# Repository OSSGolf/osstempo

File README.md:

# Tempo Trainer

A TempoStik-style tempo trainer: a WS2812B LED strip animates a swing so the
user follows a moving dot to groove their tempo. Two modes — **putting** (2:1)
and **full swing** — selectable over BLE. No audio.

## Goal

A white LED "comet" sweeps along the strip following a pendulum/arc model so the
motion feels like a real stroke. The user matches their club/putter head to the
dot to train tempo and stroke length. Reference dots (green = ball/impact,
amber = top of backswing, red = full extent, optional purple = full-swing
weight-shift aim) orient the golfer before each rep.

- **Putt mode:** comet sweeps center → amber (backswing), eases to a stop, then
  accelerates back through center (impact) and out the far side (follow-through).
- **Full mode:** models a full swing's *arc projected onto the 1D strip* (see
  [Animation models](#animation-models)). Lets a 1 m strip represent a swing that
  goes back and up behind the golfer.

## Build guides

Two ways to build it, same firmware and app. See [`docs/`](docs/):

- [**docs/full-diy/**](docs/full-diy/) - bare ESP32 dev board, strip, one resistor
  and one cap on a breadboard. Lowest cost.
- [**docs/dig2go/**](docs/dig2go/) - pre-assembled [QuinLED-Dig2go]. Screw in three
  wires, flash, done.
- [**pcb/**](pcb/README.md) - the ESP32 carrier PCB (v1.2): the dev board drops into two
  sockets, JLCPCB places the passives, you hand-solder eleven marked pins. Renders, build
  pipeline and the JLCPCB order files live there; [`pcb_build_spec.md`](pcb_build_spec.md)
  is the board spec.

Each folder has a bill of materials, a wiring and flashing guide, and a pinned,
ready-to-flash sketch. The sections below are the full hardware and firmware spec
that both builds share.

[QuinLED-Dig2go]: https://quinled.info/quinled-dig2go/

## Hardware

- **MCU:** ESP32 classic (ESP-WROOM-32, 30-pin dev board, micro-USB). BLE used, not WiFi.
  USB-UART chip is a **CP2102** (Silicon Labs).
- **LED strip:** WS2812B, **144 LEDs on a ~1 m strip (144 LEDs/m)**, bare PCB
  12 mm wide x 2.2 mm tall, 5 V. (~0.69 cm per LED; half-strip ≈ 50 cm each side.)
- **Mounting:** 12 mm aluminum LED channel with frosted diffuser (self-sourced).
  2020 extrusion was rejected as the light channel (T-slot opening ~6 mm is too
  narrow for the 12 mm strip, and bare aluminum gives no diffusion).
- **Power:** micro-USB from a power bank or 5 V wall adapter. **A 2 A supply is
  recommended.** The strip is powered through the board's 5 V passthrough pin.
  The comet animation is low-draw (~100-300 mA), so the full-strip ~8 A worst
  case does not apply — but do **not** run an all-LEDs-on white pattern on 2 A.
- **Protoboard:** the 30-pin ESP32 is too wide for one standard breadboard — it
  straddles **two breadboards** (one row of pins on each) so the outer holes stay
  free.

## Wiring

| From | To |
|---|---|
| `GPIO5` (labeled `D5`) | 470 ohm resistor -> strip DIN |
| `VIN` pin (the 5 V passthrough; *not* `3V3`) | strip 5V (+ breadboard red rail) |
| `GND` | strip GND (common ground, blue rail) |
| 1000 uF cap | across 5V/GND at strip input (stripe / short leg to GND) |

- **`VIN` is the 5 V passthrough.** On the 30-pin board the silkscreen labels it
  `VIN` (not `5V`); it carries USB 5 V out to the strip. Do not use `3V3`.
- **Level shifter (SN74HCT245) is on hand but NOT needed** — the bare 3.3 V data
  line drives the strip cleanly (no first-pixel flicker observed). Add it on the
  `GPIO5 -> DIN` line only if flicker/wrong colors appear later.
- `GPIO5` was chosen as an exposed pin on the 30-pin board. Feed the strip at the
  DIN end (follow the data-direction arrow).

### macOS USB note

The board appears as a serial port (`/dev/cu.usbserial-*` or
`/dev/cu.SLAB_USBtoUART`) only when:

1. The **CP210x VCP driver** is installed **and approved** in
   *System Settings -> Login Items & Extensions -> Driver Extensions* (macOS
   Sequoia moved the approval there; a reboot alone does not approve it).
2. A **data-capable USB cable** is used. A charge-only micro-USB cable lights the
   board's red power LED but never enumerates on USB — the single most common
   "board not detected" cause. Verify with `ls /dev/cu.*` after plugging in.

## Firmware

- **Language / libs:** Arduino C++ (`.ino`), [FastLED], ESP32 core BLE
  (`BLEDevice` / `BLEServer`) and `Preferences` (NVS). FastLED is the only
  Library Manager install; BLE + Preferences ship with the ESP32 core.
- **Board target:** "ESP32 Dev Module."
- **Partition scheme:** **"Huge APP (3MB No OTA/1MB SPIFFS)"** — BLE + FastLED
  exceed the default app partition.
- **Upload:** micro-USB, 115200 baud. Hold **BOOT** if upload stalls at
  `Connecting...`. The sketch boots straight into the continuous loop (no BLE
  needed to run); BLE is only for customization.
- **File:** `tempo_trainer/tempo_trainer.ino`.

## Animation models

Center LED (index ~71/72) = ball / impact. Each rep runs a get-ready **countdown**
(the green impact LED pulses smoothly N times, 1 s each, with the aim dots lit) and
then the stroke, auto-repeating after a rest gap. During the stroke the comet is
**bounded** by the impact and aim markers (the green/amber "rails", toggle `000e`):
it emerges from the ball and parks at the backswing point rather than overshooting.

### Putt mode (pendulum)

1. **Get-ready countdown:** the green ball pulses smoothly N times (1 s each,
   N = `round(get-ready ms / 1000)`), with the amber aim dot lit so you can set up.
2. **Backswing:** comet center -> amber with `sin` easing (fast leaving center,
   decelerating to a stop), **bounded to `[impact, amber]`** — it emerges from the
   ball and parks at the amber without overshooting either marker.
3. **Drop to impact:** comet amber -> center over `downswing ms` (the tempo
   number; ratio = backswing:downswing), shaped by `release`. Fastest at impact;
   flows **through** impact (no hitch) into the follow-through.
4. **Follow-through:** center -> `-reach` over `follow-thru ms`, decelerating.
5. **Hold** at the finish, then **rest**, repeat.

With `rails lit` (`000e`) on, the green impact and amber backswing dots stay lit
throughout as the bounding "walls"; off, the amber shows until reached (legacy look).

### Full mode (arc projected onto the strip)

A full swing's clubhead traces an arc. Projected onto the 1D strip its position
is **non-monotonic**: it reaches max width (**red**, at the strip end) around
waist height, then comes up/in to the top of backswing (**amber**, inboard of
red). The downswing retraces back out to red before dropping to impact.

```
 followRed              center            amber          backRed
   (red)                (green)          (amber)          (red)
   |---------------------|----------------|----------------|
   far end             impact         top of back       near end / max width

 1. Backswing:   center -> backRed -> backAmber       (out to max width, up to top)
    [top pause]
 2. Downswing:   backAmber -> backRed -> center        (back out, then to impact)
 3. Follow-thru: center -> followRed                   (to the far end; no follow amber)
 4. Hold, rest, repeat
```

Easing keeps velocity zero at the turnarounds (both red visits, the top) and
maximal at center (impact), so the projection reads like a real swing.

#### Aiming dot (purple, full swing, optional)

An optional **purple** secondary dot (`000f`-`0011`, per-mode, full only) gives a
weight-shift / hit-down reminder for irons. It defaults **off**; when enabled it
sits 2 LEDs to the **target side** of impact (toward the finish) and never overlaps
the ball, amber, or red dots. It **appears** at a configurable stroke moment (`0011`: 0 address / 1 top
of backswing (default) / 2 start of downswing / 3 impact) and **stays lit until the
next rep**, independent of the `rails lit` toggle. Position (`0010`) is any LED that
is not already a marker.

### Release (acceleration profile)

Per Grober's pendulum framework, the dominant acceleration lever is the **tempo
ratio** (backswing:downswing) — already exposed via the two times. The one
remaining physical degree of freedom is the **release / lag**: how the downswing's
speed builds between the top and impact. `release` (`000c`, per-mode) blends the
drop-to-impact from a **free pendulum** (0: smooth, velocity peaks gently at
impact, putting-like) to a **late lag release** (100: the comet hangs near the top,
then snaps through impact). It reshapes only the drop-to-impact segment and never
changes tempo (impact still lands on time). Defaults: putt 0, full 55.

## Profiles & persistence

- **Two profiles** (putt / full), each with its own `backswing ms`,
  `downswing ms`, `reach`, and `top-hold ms`. Switching mode restores that mode's
  settings.
- **Global settings** (shared): brightness, get-ready ms, finish-hold ms, rest ms.
- All settings are **persisted to flash (NVS)** and reload on boot. Writes are
  debounced (~1.5 s) so live preview-slider dragging doesn't wear the flash.
- `control` is **not** persisted — the device always boots into loop mode.

#### Reversing the stick (180 flip)

`0014` runs the stroke the other way down the strip, for a left-hander or a stick lying the
other way round. It mirrors the **finished frame** on its way out, `i -> NUM_LEDS-1-i`, at the
firmware's single output choke point (`showFrame()`), so every element flips together -- comet
head and tail, green ball, amber top-of-backswing, both red extents, the purple aim dot, the
get-ready pulse, the idle dot -- and nothing in the stroke math changes. Reflection about index
`(NUM_LEDS-1)/2` *is* reflection about `CENTER`, so the picture stays self-consistent; the green
ball sits half an LED above centre normally and half an LED below it reversed, which is the exact
mirror image rather than an off-by-one.

Flipping mid-stroke is safe and needs no special handling: the renderer holds no temporal state,
so frame N draws logical and frame N+1 draws mirrored, both at the same cycle time. The comet
lands at its mirror position with identical phase -- a reflection in space, never a jump in time.
Worst case it is visible one render tick later (<=12 ms while running, <=20 ms idle), plus the
BLE round trip; a phone write with response is typically another 60-130 ms.

Two states would otherwise give no feedback at all -- idle lights a single dim centre pixel, and
the rest gap lights nothing -- so for 1.2 s after a flip both paint the mode's static dot map
instead. The amber dot jumping to the other side of the ball is the answer to "which way does it
run now?".

**It is device-local.** Orientation describes how *that* stick is lying, so it is deliberately
not carried in the sync beacon: two sticks in a set can point opposite ways, and a leader can
never rotate a follower's strip. Consequence: a follower goes BLE-quiet while in a set, so set
orientation **before** joining. It persists in NVS, including across a follower's revert.

It is also the one characteristic the iOS app treats as **optional**, so a stick flashed before
`0014` existed still connects and works -- only the reverse toggle is disabled.

## BLE GATT

- **Service:** `6e400001-b5a3-f393-e0a9-e50e24dcca9e`
- **Device name:** `PuttTempo`

| UUID tail | Param | Type | Range / units | Scope | Default (putt / full) |
|---|---|---|---|---|---|
| 0002 | backswing ms | uint16 LE | 100-5000 | per-mode | 700 / 900 |
| 0003 | downswing ms (top→impact) | uint16 LE | 100-5000 | per-mode | 350 / 300 |
| 0004 | reach (amber) | uint8 | 1-71 LEDs from center | per-mode | 58 / 60 |
| 0005 | brightness | uint8 | 0-255 | global | 40 |
| 0006 | control | uint8 | 0 idle / 1 loop / 2 single / 3 preview | runtime | 1 |
| 0007 | get-ready ms | uint16 LE | 0-10000 (countdown: round(ms/1000) impact pulses) | global | 1000 |
| 0008 | finish hold ms | uint16 LE | 0-10000 | global | 600 |
| 0009 | rest ms | uint16 LE | 0-20000 | global | 3000 |
| 000a | mode | uint8 | 0 putt / 1 full | persisted | 0 |
| 000b | top-hold ms | uint16 LE | 0-2000 | per-mode | 0 / 150 |
| 000c | release | uint8 | 0-100 (0 pendular .. 100 lag) | per-mode | 0 / 55 |
| 000d | follow-thru ms | uint16 LE | 0-10000 (impact→finish) | per-mode | 350 / 300 |
| 000e | rails lit | uint8 | 0/1 (keep impact+aim dots lit) | global | 1 |
| 000f | aim2 enabled | uint8 | 0/1 (purple weight-shift dot, full only) | per-mode | 0 / 0 |
| 0010 | aim2 position | uint8 | 1-142 (absolute LED index) | per-mode | 70 / 70 |
| 0011 | aim2 when | uint8 | 0 address / 1 top / 2 downswing / 3 impact | per-mode | 1 / 1 |
| 0014 | flip | uint8 | 0 normal / 1 mirrored end-for-end | global, device-local | 0 |

uint16 values are little-endian (e.g. 700 = `BC 02`). Per-mode writes apply to
whichever mode is currently selected (`000a`); switching `000a` refreshes the
per-mode characteristics so a read returns that mode's saved values.

- **`0006` (control) supports NOTIFY** — subscribe to get device-side state
  changes pushed (e.g. a single stroke auto-resetting to idle).
- **Discovery:** the device advertises the **service UUID** (filter scans on it)
  and broadcasts the name `PuttTempo` in the scan response. iOS/CoreBluetooth
  clients should scan by service UUID, not name.

### Setting the backswing point (live preview)

1. Write `000a` = mode (`00` putt / `01` full).
2. Write `0006` = `03` (preview) -> the strip shows the static dot map.
3. Write `0004` = reach in LEDs and watch the **amber dot move live**; park it
   where the backswing should stop.
4. Write `0006` = `01` (loop) -> runs strokes; the value auto-saves ~1.5 s later.

Drive it from a phone with **nRF Connect** (scan -> connect to `PuttTempo` ->
write characteristics), or a Web Bluetooth page (TODO below).

## Clients

- **Web Bluetooth page** (`web/index.html`) — single self-contained control page.
- **iOS app** (SwiftUI + CoreBluetooth) in the
  [osstempo-ios repo](https://github.com/OSSGolf/osstempo-ios) —
  native controller with numeric tuning (tap to type or hold to adjust), per-value
  strip diagrams, a follow-through link, a live reach drag, the get-ready countdown /
  rails toggle, and the on-strip stroke visualizer. Dev-only (no App Store).

## Gotchas / lessons learned

- **GATT handle budget.** ESP32 Arduino `createService(uuid)` defaults to **15 handles**
  and *silently truncates* the characteristic table after ~7 chars, and the Arduino BLE wrapper
  does not check the error. Symptom: a client discovers only the first 6-7 characteristics and
  rejects the device as incompatible -- indistinguishable from the stale-GATT-cache symptom
  below, so you pay the debugging cost twice. Count it exactly every time you add one:
  1 (service) + chars x 2 + 1 per CCCD. Today that is `1 + 19x2 + 2 = 41`, against the 48
  reserved by `createService(BLEUUID(SVC_UUID), 48)` -- room for 3 more before it must rise.
- **`FastLED.show()` must appear exactly once**, inside `showFrame()`. That is what makes the
  180 flip total: the mirror is applied to the finished buffer, so no LED element can escape it
  -- but only while every render path latches through that one function. `FastLED.clear(true)`
  is banned for the same reason (it calls `showColor()`, a second output path that bypasses the
  frame buffer entirely), as is `FastLED.clear()` (it clears the array bound to the controller,
  which is the *physical* buffer, not the logical frame -- use `clearLeds()`).
  `firmware_tests/check_show_chokepoint.sh` enforces all of this; a compile cannot.
- **`FastLED.show()` returns before the strip is latched.** It is asynchronous, and its internal
  yield can deschedule the calling task for milliseconds. The renderer composes into `leds[]` and
  `showFrame()` copies that into a separate `physLeds[]` for FastLED, so the shared frame is never
  transiently inconsistent -- which is why the flip does not mirror `leds[]` in place.
- **iOS caches the GATT table.** After adding/removing a characteristic and re-flashing,
  iOS serves the *stale* cached service list — toggle the iPhone's Bluetooth off/on (or forget
  the device) to force fresh discovery, or you'll see the old characteristic set.
- **Brightness 0 bricks the strip across reboots.** `brightness` is persisted and was not
  floored on load, so a persisted 0 made the strip invisibly dark on every boot. `loadParams()`
  now floors it (`constrain(brightness, 8, 255)`); runtime writes can still go dimmer.
- **Comet tail direction** is inferred from `prevPos` and lags ~1-2 frames at zero-velocity
  turnarounds; harmless given the bounding clip. (Was previously a visible cosmetic issue.)
- **Full-mode follow-through has no inboard finish marker** by design.

## Tests

Host-compiled, no hardware needed:

```
cc -O2 -o /tmp/golden firmware_tests/golden_kinematics.c -lm && /tmp/golden
cc -O2 -o /tmp/flip   firmware_tests/flip_mirror.c      -lm && /tmp/flip
sh firmware_tests/check_show_chokepoint.sh
node web/check_flip_mapping.js
```

Compile gate, **both** boards (they must both build; the flip touches no board-conditional code):

```
arduino-cli compile --fqbn "esp32:esp32:esp32:PartitionScheme=huge_app" --warnings all tempo_trainer
arduino-cli compile --fqbn "esp32:esp32:esp32:PartitionScheme=huge_app" --warnings all \
  --build-property "compiler.cpp.extra_flags=-DBOARD_DIY_ESP32" tempo_trainer
```

### Bench checklist for the flip (not yet run)

None of the above touches the flashed binary, so these still need a stick. Run on **both**
boards -- the Dig2go and the generic ESP32:

1. Flip mid-backswing while looping: the comet reflects with no phase jump and no tearing.
2. Flip during the dark rest gap, and while idle: the dot map appears for ~1.2 s and the amber
   dot is on the opposite side of the green ball.
3. Flip during the get-ready countdown.
4. Flip while `control == 2` (single) and let the stroke auto-return to idle.
5. **Flip, then pull the power while still looping, then reboot** -- orientation must survive.
   This is the case the rest-gap commit exists for; the stick has no power button.
6. Flip, join a set as a follower, disband, and confirm orientation survived the revert.
7. Blink-to-find while looping, before and after: the strip must never be left reversed.
8. Hammer `0014` at ~50 Hz from nRF Connect for a minute while looping, then stop: the strip
   must not end up stuck reversed.
9. Connect the iOS app to a stick flashed with the *old* firmware: it must still connect, with
   only the reverse toggle disabled.
10. Change a tuning value and form/join a set within ~1 s, then disband: the edit must survive.
    Session formation now defers to the render core so it can commit first, so this also confirms
    the deferral still forms the set when the app drops BLE immediately after the write.
11. Tap Blink-to-find twice in quick succession: both taps must blink.

## Current state

Working sketch implements everything above. **Tested on hardware end-to-end** with the iOS
app: discovery by service UUID, full 16-characteristic sync, live reach preview, mode switch,
transport control, the get-ready countdown, and the bounded comet on the strip.

[FastLED]: https://github.com/FastLED/FastLED

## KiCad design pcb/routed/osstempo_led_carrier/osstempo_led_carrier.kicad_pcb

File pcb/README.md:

# osstempo PCB source

Board source for the ESP32 carrier PCB described in [`../pcb_build_spec.md`](../pcb_build_spec.md).
**That spec is the authority** on what the board is; this directory is how it gets built.

## What it looks like (v1.2)

| Front - component side | Back - the side you solder |
|---|---|
|  |  |

The ESP32 dev board plugs into the two sockets on the front, USB toward the `▲ USB` mark, and
JLCPCB places the resistor and the six 22 µF caps. The back is the hand-soldering side: an
arrow marks each of the eleven pins to solder (the four that carry a net, four more at the
socket ends for strength, the three LED-connector pins), every used pin is labelled, and the
rest is a 42 mm golf ball with the logo. The socket pads are 2.0 mm round, a 0.5 mm annular
ring, so there is copper to rest the iron on:

### Why the back has no copper plane: v1.0 vs v1.2

| v1.0 back | v1.2 back |
|---|---|
|  |  |

v1.0 had a solid ground plane on the back (the olive tint) and a ground pour on the front,
tied solid to the ground pins. In practice no socket pad would heat enough for solder to wet
it at 350-420 °C; the joints only took with a heat gun on the whole board. v1.1 removed every
pour, so each through-hole pin touches at most one trace; v1.2 adds the solder-side
silkscreen, the 2.0 mm pads, and drops every designator.

Renders come from `sh pcb/render.sh` (current release) or
`sh pcb/render.sh <file.kicad_pcb> <label>` (any revision, e.g. the v1.0 archive).

## The toolkit is a private dependency, not part of this repo

The board is authored with the
[kicad-agent-toolkit](https://github.com/georgemclaughlin/kicad-agent-toolkit) — a
**private, separately-licensed repo** checked out at `../../kicad-agent-toolkit`. Nothing
from it is vendored here: no source, no config, no example boards. `pcb/.ci/toolchain.json`
(its version-pin file) is gitignored and copied in by `setup-toolkit.sh`. If you don't have
access to the toolkit you can still open `routed/<board>/` in KiCad and send
`routed/<board>/` gerbers to a fab; you just can't regenerate from the YAML.

The toolkit only discovers boards under its own `examples/`, but `KICAD_AGENT_PROJECT_ROOT`
repoints it at an arbitrary board root — which is what `env.sh` does. An out-of-tree root
reproduces byte-identical results to running inside the toolkit repo.

### Toolkit branch `osstempo-patches-v2`

The board builds on a local branch of the toolkit clone: upstream `main` (fetched 2026-11-03)
plus the patches this board needs, each with tests and a docs page (`setup-toolkit.sh`
checks it out). They are general and belong upstream as PRs:

1. **Fill zones when autoroute is disabled.** With `autoroute.enabled: false` (the only
   option on macOS, below) the pipeline returned before any zone fill, so the saved board -
   and the gerbers - had zone outlines with no ground plane. Moot for v1.2 (no zones), still
   true upstream.
2. **`board.artwork`** - place a pad-less silkscreen footprint (the golf ball) without a
   reference label. Upstream's own `board.silkscreen_artwork` wants polygons inline in the
   manifest; a 143-outline TrueType rendering belongs in a footprint file.
3. **`mounting_holes[].hide_reference`** - drop the `MHn` labels.
4. **`pcb_no_reference_label`** on a component: no designator on the board at all. The
   toolkit draws its own `Cn`/`Rn`/`Hn` silkscreen label for every placed part
   (`pcb_hide_reference` only hides the footprint's built-in one, and the toolkit's tests rely
   on that meaning). A branded board with machine-placed passives wants neither - JLC places
   from the CPL, not the silkscreen.
5. **`board.zones[].pad_connection`** - thermal reliefs (`thru_hole_only`) for any future
   board that keeps a pour and still hand-solders its through-hole pins.
6. **`tht_hand_solder_heat`** layout-quality check - the hand-soldering heat model
   (`docs/framework/evidence/hand-solder-heat.md` in the toolkit). Declared in this board's
   `layout/osstempo_led_carrier_layout_quality.yaml`.

Retired: the `outline.corner_radius` patch. Upstream has `corner_radius_mm` since October;
it draws each corner as eight short edge segments where the patch drew one true arc, which is
the only difference between the ordered v1.2 gerbers and a rebuild on this branch.

The previous branch `osstempo-patches` (September upstream base) built the ordered v1.0 to
v1.2 releases and has been deleted; the zip committed in `build/jlcpcb_order/` is the one
uploaded to JLCPCB, and a rebuild on this branch reproduces it except for the Edge_Cuts
corners (`build.sh` rewrites the zip, so restore it from git after a rebuild unless the board
changed). Upstream moved under it in ways this board had to follow: the board source must record
[design-consideration decisions](examples/osstempo_led_carrier/osstempo_led_carrier_design_considerations.yaml),
every passive needs sourced nominal facts and ratings bound to a retained, hash-bound
datasheet under `vendor_ecad/datasheets/`, and rule-pack passive checks name a `part` kind
instead of a symbol. The `board considerations` report command still expects the toolkit's
block catalogue under the board root and does not run out-of-tree; validation does.

## Layout

```
pcb/
  env.sh                     source this first
  setup-toolkit.sh           one-time: toolkit branch, venv, ngspice, podman, KiBot image
  build.sh                   the build: validate x2, reseed, JLC order; stops the podman VM on exit
  reseed-routed.sh           copy the promoted release into routed/ and re-run DRC
  render.sh                  3D renders of routed/ (or any .kicad_pcb) -> renders/
  routed/<board>/            the accepted release, writable - what you OPEN and what goes to fab
  renders/                   the README images: v1.0 and v1.2 both sides, socket-pad close-up
  examples/<board>/          board source: manifest, artwork/, component usage/knowledge, emc/,
                             layout/, spice/
  component_packs/           our exact-part records (LCSC ids, footprint/model digests) + rule pack
  vendor_ecad/               only the official KiCad symbols/footprints/3D models the board uses,
                             plus our generated footprints; provenance in each README
  vendor_ecad/datasheets/    retained, hash-bound datasheets the component packs cite
  tools/make_logo_footprint.py    silkscreen artwork (spec JSON + fonts) -> polygon footprint
  tools/make_socket_footprint.py  official 15-way socket -> the 2.0 mm-pad copy for hand soldering
  tools/make_jlc_order.py         promoted release -> the JLCPCB upload set (zip + BOM + CPL)
  bin/podman                 shim: forces --platform linux/amd64 for the KiBot image
  design_blocks/             unused (authored-copper board needs none)
  .ci/toolchain.json         toolkit's version pins - gitignored, copied by setup
  build/jlcpcb_order/        the JLCPCB upload set for the current revision - committed
  build/v1.N-archive/        earlier revisions' order sets (v1.0 also keeps its routed board)
  build/kicad-agent/         the toolkit's run/release trees - gitignored, 300+ MB, regenerated
```

## Usage

```sh
sh pcb/setup-toolkit.sh                       # once
sh pcb/build.sh                               # the whole build; stops the podman VM when it exits
```

`build.sh` runs `board validate` twice (the second identical run promotes the release),
reseeds `routed/`, writes the JLCPCB order set, and **always stops the Podman VM** on exit -
the KiBot container needs the VM, but idle it pins 2 CPU cores and 4 GB of RAM. Run the
steps by hand only when debugging one of them:

```sh
source pcb/env.sh
$KICAD_AGENT board validate osstempo_led_carrier   # build + ERC/DRC + every evidence gate
$KICAD_AGENT board validate osstempo_led_carrier   # second matching run promotes the release
sh pcb/reseed-routed.sh osstempo_led_carrier  # sync build/.../current -> routed/, DRC
podman machine stop                           # build.sh does this for you
```

### Ordering from JLCPCB

```sh
python3 pcb/tools/make_jlc_order.py           # -> pcb/build/jlcpcb_order/
```

Turns the promoted release into the three things jlcpcb.com asks for: a gerber+drill zip, a
BOM CSV keyed by LCSC part number, and a CPL in JLC's column/units convention. It checks every
release file against `fabrication_manifest.json` first, and the zip is byte-reproducible.

Which parts JLC places is read off the board, not listed in the script: a footprint is an
assembly part **iff it has a `JLCPCB Part #` property**, so the hand-soldered H1/H2/J1 drop out
of both CSVs on their own.

It also makes the package uploadable, so **never send the release's gerbers to JLCPCB
directly** - its parser stalls at ~96% on them. Two things are wrong and both needed fixing:

1. The reproducibility pass normalises every `CreationDate` to the literal string `<normalized>`
   in the *shipped artifacts*, not just in the hash input, leaving an invalid X2 header. This
   belongs upstream as a PR alongside the `osstempo-patches-v2` patches: normalise for hashing,
   emit a real date.
2. JLCPCB does not digest the X2 attributes or the `.gbrjob` at all, so the script strips both by
   default (gerbers only - the drill's X2 comments carry the NPTH marking). `--x2` keeps them. The quote-page and assembly settings are tabulated in
[`../pcb_build_spec.md`](../pcb_build_spec.md) under "JLCPCB order notes".

Copper is authored in the manifest (`board.routes`, `board.vias`, `board.ground_stitching`,
`board.zones`), so the whole board regenerates from YAML. **Never edit generated `.kicad_*`
files** — change the YAML and re-validate. Two consecutive validate runs with identical
inputs promote an immutable release under `build/kicad-agent/<board>/current/`; its
`fabrication/` directory is the JLCPCB package.

**Never open KiCad on anything under `build/`.** Run and release trees are sealed; the
`.lck` files KiCad drops beside a project void a promotion mid-flight. Open `routed/<board>/`.

## macOS caveats (KiCad 10.0.6, established empirically)

- **`kicad-agent doctor` reports BLOCKED — ignore it.** It wants the exact versions in
  `.ci/toolchain.json` by string equality. It does not gate `board build`/`validate`.
- **Autorouting does not work on macOS** — the toolkit re-executes itself under KiCad's
  bundled Python, which is 3.9 here, and its parser uses 3.10 syntax (`DSN_EXPORT_FAILED`).
  Hence authored copper.
- **Fabrication export needs Podman** (Docker is rejected) and the pinned KiBot image is
  amd64-only; `bin/podman` adds `--platform linux/amd64`. First run pulls ~1 GB.
- `TMPDIR` must be symlink-free and outside the project root (`env.sh` resolves it).

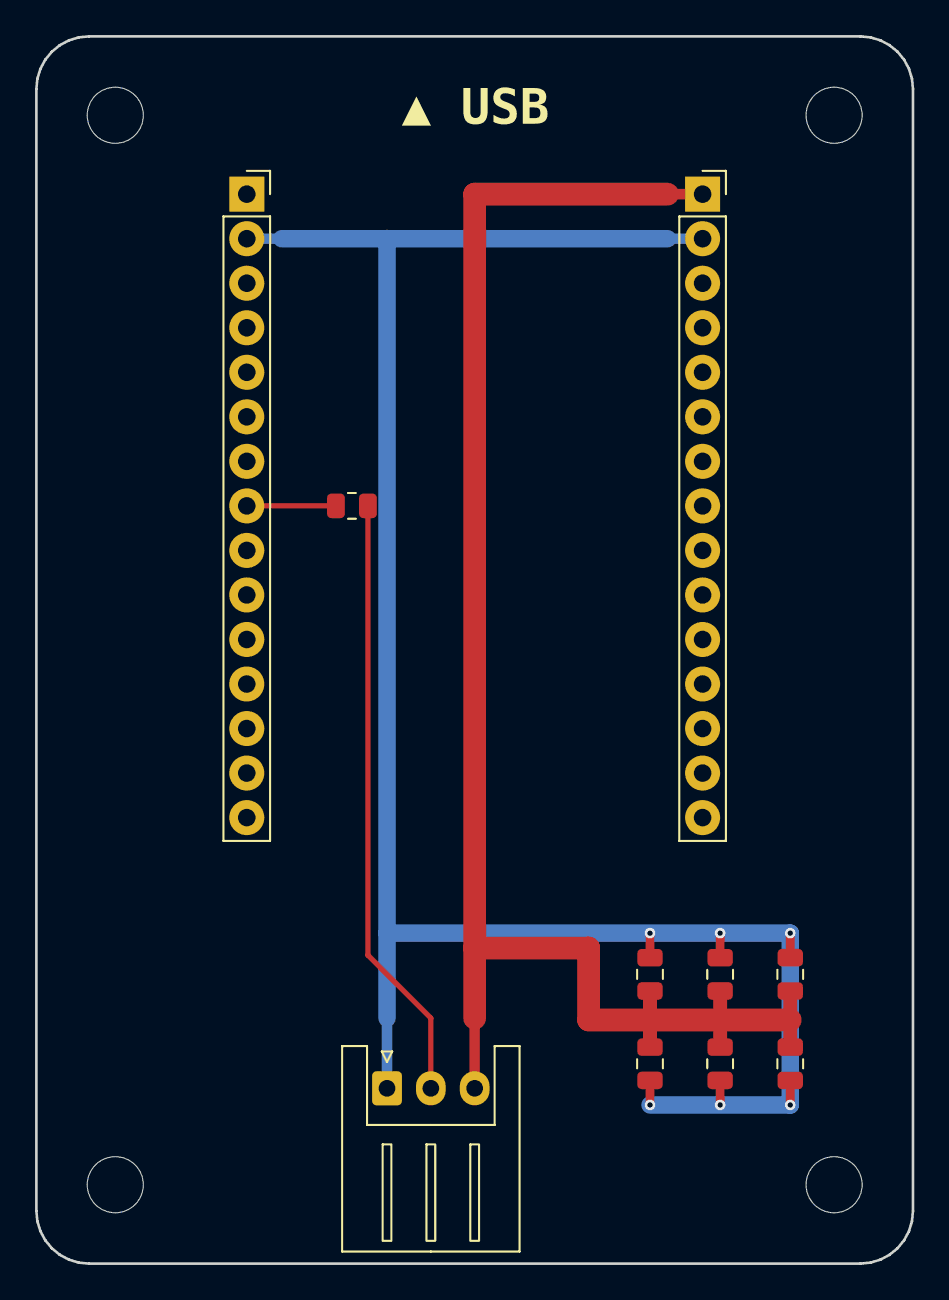
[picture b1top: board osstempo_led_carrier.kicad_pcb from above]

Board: 2 copper layers, 50.0 x 70.0 mm, 16 parts (1 on the bottom side), 4 nets.

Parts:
C1, C2, C3, C4, C5, C6: 22uF; C_0805_2012Metric
H1, H2: ESP32_SOCKET; PinSocket_1x15_P2.54mm_Vertical_Pad2.0
J1: LED_OUT; JST_XH_S3B-XH-A_1x03_P2.50mm_Horizontal
MARK1: ▲ USB; Mark_USB_End
MH1, MH2, MH3, MH4: MountingHole_3.2mm
R1: 470R; R_0805_2012Metric
SILK1: arrow / arrow / GND / arrow / D5 / arrow / arrow 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; Silk_Back_v1_2

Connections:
5V: C1.1, C2.1, C3.1, C4.1, C5.1, C6.1, H2.1, J1.3
DIN: J1.2, R1.2
ESP32_IO5: H1.8, R1.1
GND: C1.2, C2.2, C3.2, C4.2, C5.2, C6.2, H1.2, H2.2, J1.1
